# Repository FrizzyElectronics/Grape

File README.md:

# Grape

Grape es un Arduino&trade; compatible de fabricacion y diseño español. Destaca frente a otras placas por su rapidez de conexionado y por no necesitar el uso de protoboard para realizar los proyectos.

## Rasgos destacados

  - Conexion micro-USB
  - Corriente max de salida (5V) 2A
  - Pines de conexión rápida
  - Interruptor de encendido-apagado
  - 8 pines analogicos
  - Compatible con los shields de Arduino&trade; y con Arduino&trade; IDE

## Documentacion 

* **/Hardware** - Archivos de diseño en KiCad e Eagle, esquema en PDF
* **/Production** - Gerbers, BOM
* **/Design** - Logos, SVG 

Licencia
-------------------

Este producto es  **open source**! 

Por favor, revisa el archivo [LICENSE.md](https://github.com/FrizzyElectronics/Grape/blob/master/License.md) para más información. 

Si tiene alguna duda acerca del uso de esta licencia contatanos a traves de  info@frizzy.es

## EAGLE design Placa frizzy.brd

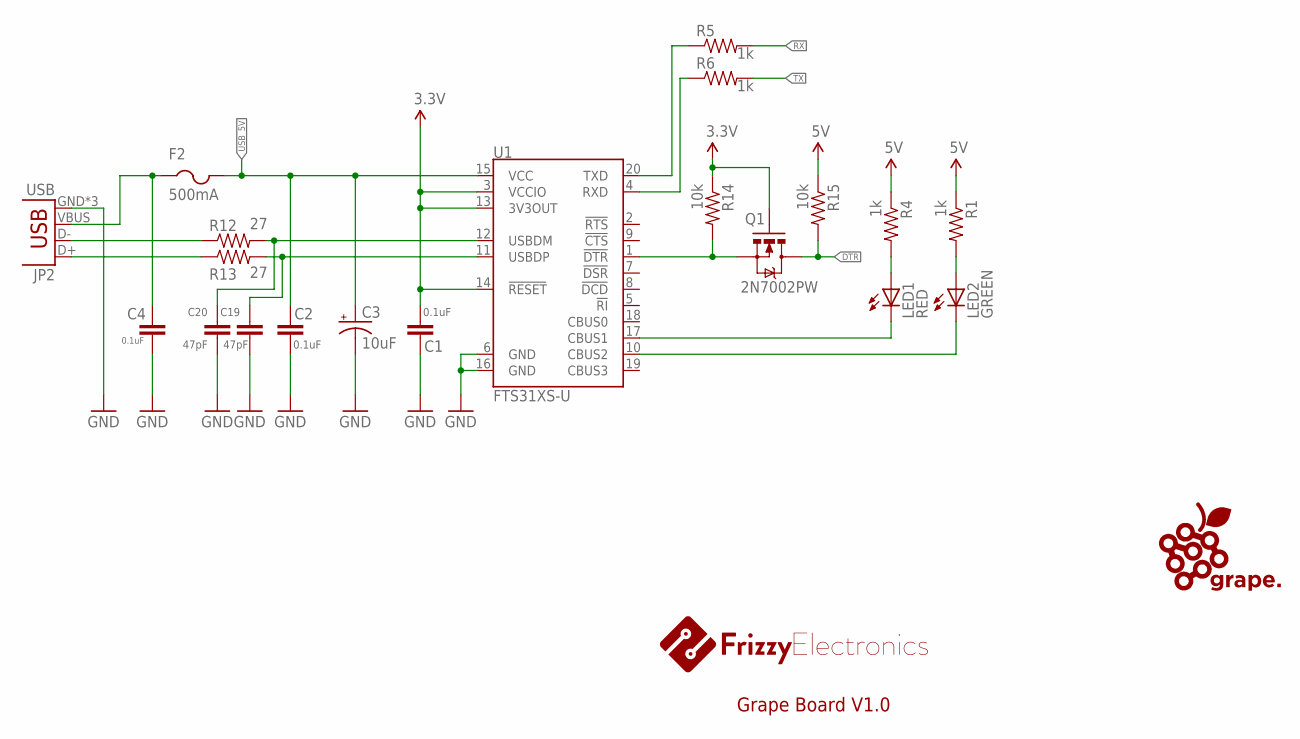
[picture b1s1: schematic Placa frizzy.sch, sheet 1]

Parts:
C1, C2, C4: 0.1uF; 0805
C3: 10uF; EIA3216
C19, C20: 47pF; 0805
F2: 500mA; 1812
JP2: USB; USB-MICROB
LED1: RED; CHIP-LED0805
LED2: GREEN; CHIP-LED0805
Q1: 2N7002PW; SOT323
R1, R4, R5, R6: 1k; 0805
R12, R13: 27; 0805
R14, R15: 10k; 0805
U1: FTS31XS-U; SSOP20_L

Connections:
3.3V: C1.2, Q1.1 (G), R14.1, U1.3 (VCCIO), U1.13 (3V3OUT), U1.14 (!RESET); also elsewhere on the board
DTR: Q1.3 (D), R15.2; also elsewhere on the board
GND: C1.1, C2.1, C3.C (-), C4.2, C19.1, C20.1, JP2.GND, JP2.MT1 (GND), JP2.MT2 (GND), U1.6 (GND), U1.16 (GND); also elsewhere on the board
unnamed: LED1.C, U1.17 (CBUS1)
unnamed: LED2.C, U1.10 (CBUS2)
unnamed: LED1.A, R4.2
unnamed: LED2.A, R1.2
unnamed: R5.1, U1.20 (TXD)
unnamed: R6.1, U1.4 (RXD)
unnamed: C20.2, R12.2, U1.12 (USBDM)
unnamed: Q1.2 (S), R14.2, U1.1 (!DTR)
unnamed: C19.2, R13.2, U1.11 (USBDP)
unnamed: JP2.D-, R12.1
unnamed: JP2.D+, R13.1
unnamed: C4.1, F2.1, JP2.VBUS
RX: R5.2; also elsewhere on the board
TX: R6.2; also elsewhere on the board
USB_5V: C2.2, C3.A (+), F2.2, U1.15 (VCC); also elsewhere on the board

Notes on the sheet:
Grape Board V1.0

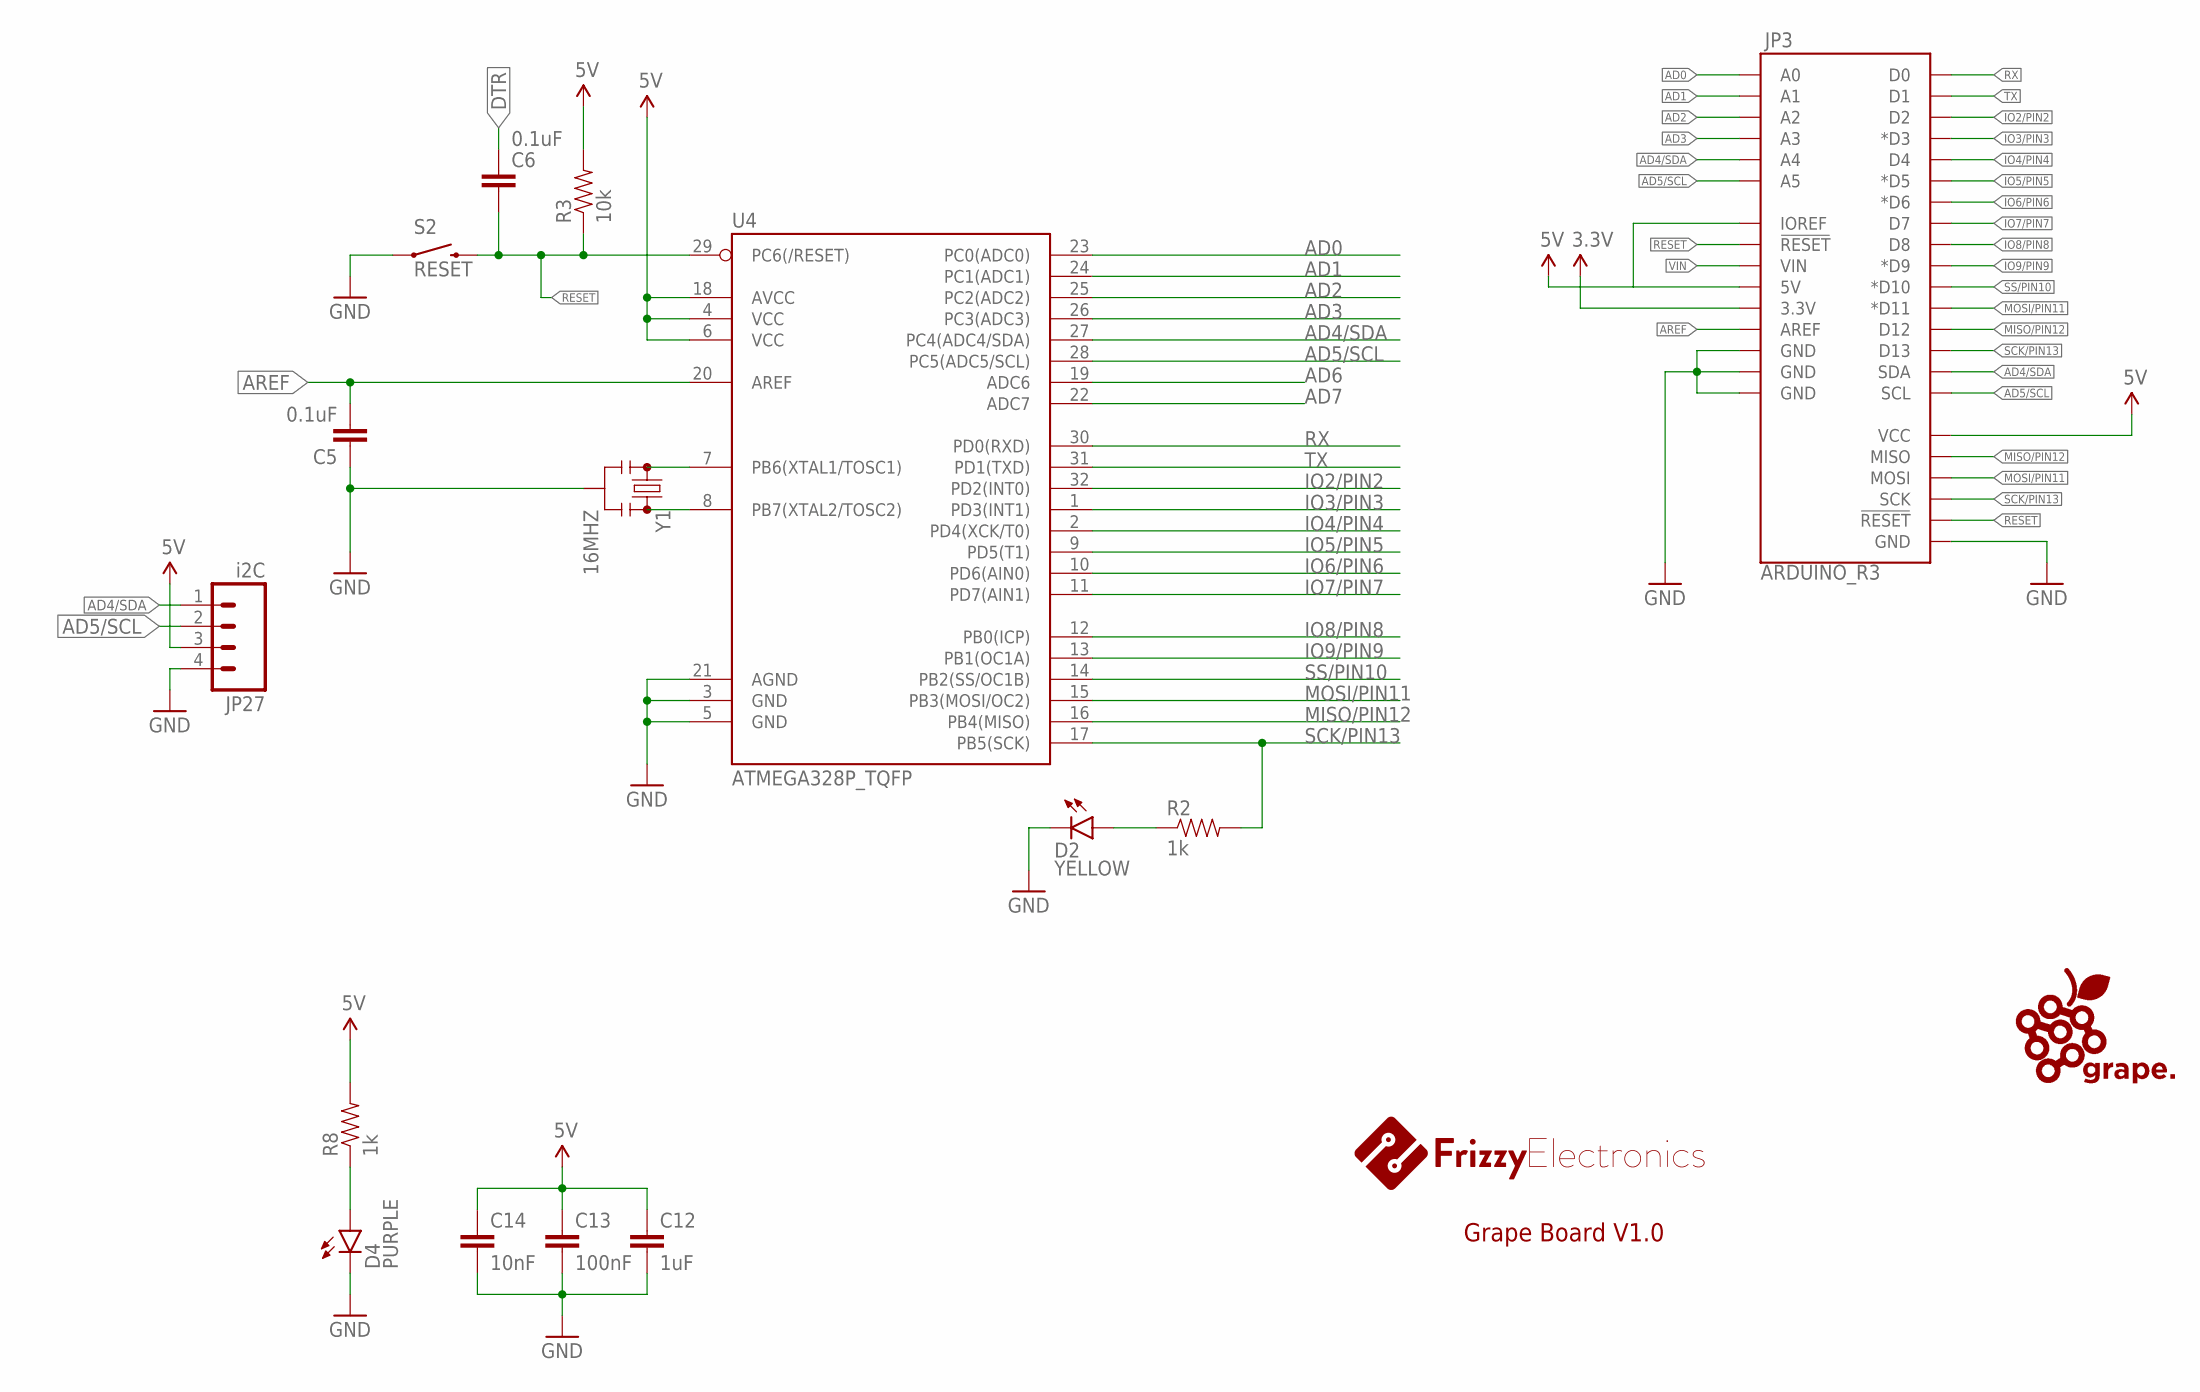
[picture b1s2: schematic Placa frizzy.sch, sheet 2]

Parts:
C5, C6: 0.1uF; 0603-CAP
C12: 1uF; 0603-CAP
C13: 100nF; 0603-CAP
C14: 10nF; 0603-CAP
D2: YELLOW; LED-0603
D4: PURPLE; LED-0603
JP3: ARDUINO_R3
JP27: i2C; JST-4-PTH
R2, R8: 1k; 0805
R3: 10k; 0805
S2: RESET; TACTILE-PTH-SIDEEZ
U4: ATMEGA328P_TQFP; TQFP32-08
Y1: 16MHZ; RESONATOR-SMD

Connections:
3.3V: JP3.3.3V; also elsewhere on the board
AD0: JP3.A0, U4.23 (PC0(ADC0)); also elsewhere on the board
AD1: JP3.A1, U4.24 (PC1(ADC1)); also elsewhere on the board
AD2: JP3.A2, U4.25 (PC2(ADC2)); also elsewhere on the board
AD3: JP3.A3, U4.26 (PC3(ADC3)); also elsewhere on the board
AD4/SDA: JP3.A4, JP3.SDA, JP27.1, U4.27 (PC4(ADC4/SDA)); also elsewhere on the board
AD5/SCL: JP3.A5, JP3.SCL, JP27.2, U4.28 (PC5(ADC5/SCL)); also elsewhere on the board
AD6: U4.19 (ADC6); also elsewhere on the board
AD7: U4.22 (ADC7); also elsewhere on the board
AREF: C5.2, JP3.AREF, U4.20 (AREF)
DTR: C6.1; also elsewhere on the board
GND: C5.1, C12.2, C13.2, C14.2, D2.C, D4.C, JP3.GND@1 (GND), JP3.GND@2 (GND), JP3.GND@3 (GND), JP3.GND@4 (GND), JP27.4, S2.1, U4.3 (GND), U4.5 (GND), U4.21 (AGND), Y1.2; also elsewhere on the board
IO2/PIN2: JP3.D2, U4.32 (PD2(INT0)); also elsewhere on the board
IO3/PIN3: JP3.D3 (*D3), U4.1 (PD3(INT1)); also elsewhere on the board
IO4/PIN4: JP3.D4, U4.2 (PD4(XCK/T0)); also elsewhere on the board
IO5/PIN5: JP3.D5 (*D5), U4.9 (PD5(T1)); also elsewhere on the board
IO6/PIN6: JP3.D6 (*D6), U4.10 (PD6(AIN0)); also elsewhere on the board
IO7/PIN7: JP3.D7, U4.11 (PD7(AIN1)); also elsewhere on the board
IO8/PIN8: JP3.D8, U4.12 (PB0(ICP)); also elsewhere on the board
IO9/PIN9: JP3.D9 (*D9), U4.13 (PB1(OC1A)); also elsewhere on the board
MISO/PIN12: JP3.D12, JP3.MISO, U4.16 (PB4(MISO)); also elsewhere on the board
MOSI/PIN11: JP3.D11 (*D11), JP3.MOSI, U4.15 (PB3(MOSI/OC2)); also elsewhere on the board
unnamed: D2.A, R2.1
unnamed: D4.A, R8.1
unnamed: U4.7 (PB6(XTAL1/TOSC1)), Y1.1
unnamed: U4.8 (PB7(XTAL2/TOSC2)), Y1.3
RESET: C6.2, JP3.RESET@1 (!RESET!), JP3.RESET@2 (!RESET!), R3.1, S2.2, U4.29 (PC6(/RESET))
RX: JP3.D0, U4.30 (PD0(RXD)); also elsewhere on the board
SCK/PIN13: JP3.D13, JP3.SCK, R2.2, U4.17 (PB5(SCK)); also elsewhere on the board
SS/PIN10: JP3.D10 (*D10), U4.14 (PB2(SS/OC1B)); also elsewhere on the board
TX: JP3.D1, U4.31 (PD1(TXD)); also elsewhere on the board
VIN: JP3.VIN; also elsewhere on the board

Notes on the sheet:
Grape Board V1.0

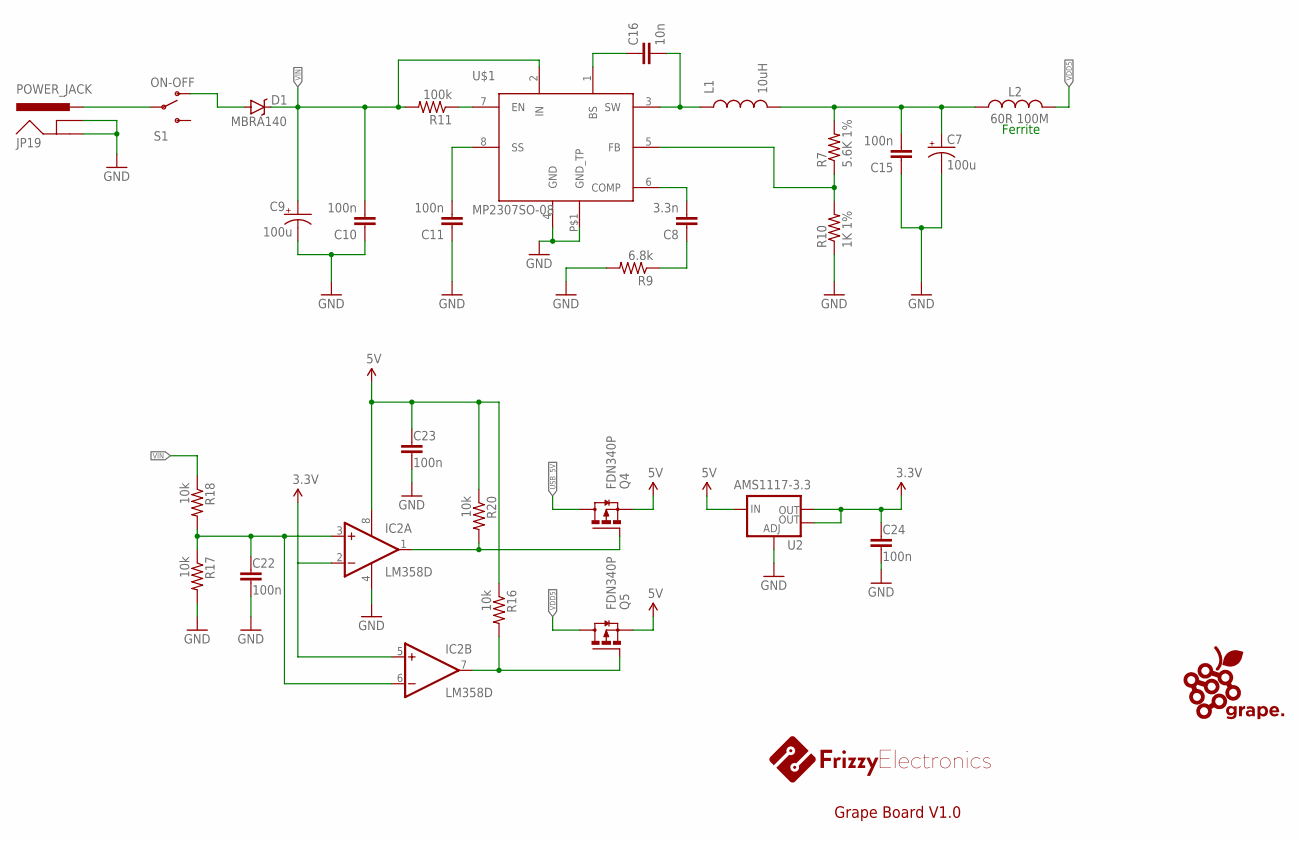
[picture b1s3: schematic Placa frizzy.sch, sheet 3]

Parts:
C7, C9: 100u; PANASONIC_D
C8: 3.3n; 0805
C10, C11, C15, C22, C23, C24: 100n; 0805
C16: 10n; 0805
D1: MBRA140; SMA-DIODE
IC2: LM358D; SO08
JP19: POWER_JACK; POWER_JACK_PTH
L1: 10uH; NPI75C
L2: 60R 100M; 0805
Q4, Q5: FDN340P; SUPER-SOT3
R7: 5.6K 1%; 0805
R9: 6.8k; 0805
R10: 1K 1%; 0805
R11: 100k; 0805
R16, R17, R18, R20: 10k; 0805
S1: ON-OFF; SWITCH-SPST-SMD-A
U2: AMS1117-3.3; SOT223
U$1: MP2307SO-08; SO-08

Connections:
3.3V: C24.1, IC2.2 (-IN), IC2.5 (+IN), U2.2 (OUT), U2.4 (OUT); also elsewhere on the board
GND: C7.-, C9.-, C10.1, C11.1, C15.1, C22.2, C23.2, C24.2, IC2.4 (V-), JP19.GND, JP19.GNDBREAK, R9.2, R10.1, R17.2, U2.1 (ADJ), U$1.4 (GND), U$1.P$1 (GND_TP); also elsewhere on the board
unnamed: C8.1, R9.1
unnamed: C8.2, U$1.6 (COMP)
unnamed: R7.1, R10.2, U$1.5 (FB)
unnamed: C16.1, U$1.1 (BS)
unnamed: C16.2, L1.1, U$1.3 (SW)
unnamed: C7.+, C15.2, L1.2, L2.1, R7.2
unnamed: C11.2, U$1.8 (SS)
unnamed: R11.1, U$1.7 (EN)
unnamed: JP19.PWR, S1.2
unnamed: D1.A, S1.1 (O)
unnamed: C22.1, IC2.3 (+IN), IC2.6 (-IN), R17.1, R18.2
unnamed: IC2.7 (OUT), Q5.1 (G), R16.2
unnamed: IC2.1 (OUT), Q4.1 (G), R20.2
USB_5V: Q4.3 (D); also elsewhere on the board
VDD5: L2.2, Q5.3 (D)
VIN: C9.+, C10.2, D1.C, R11.2, R18.1, U$1.2 (IN); also elsewhere on the board

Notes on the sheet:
Ferrite
Grape Board V1.0

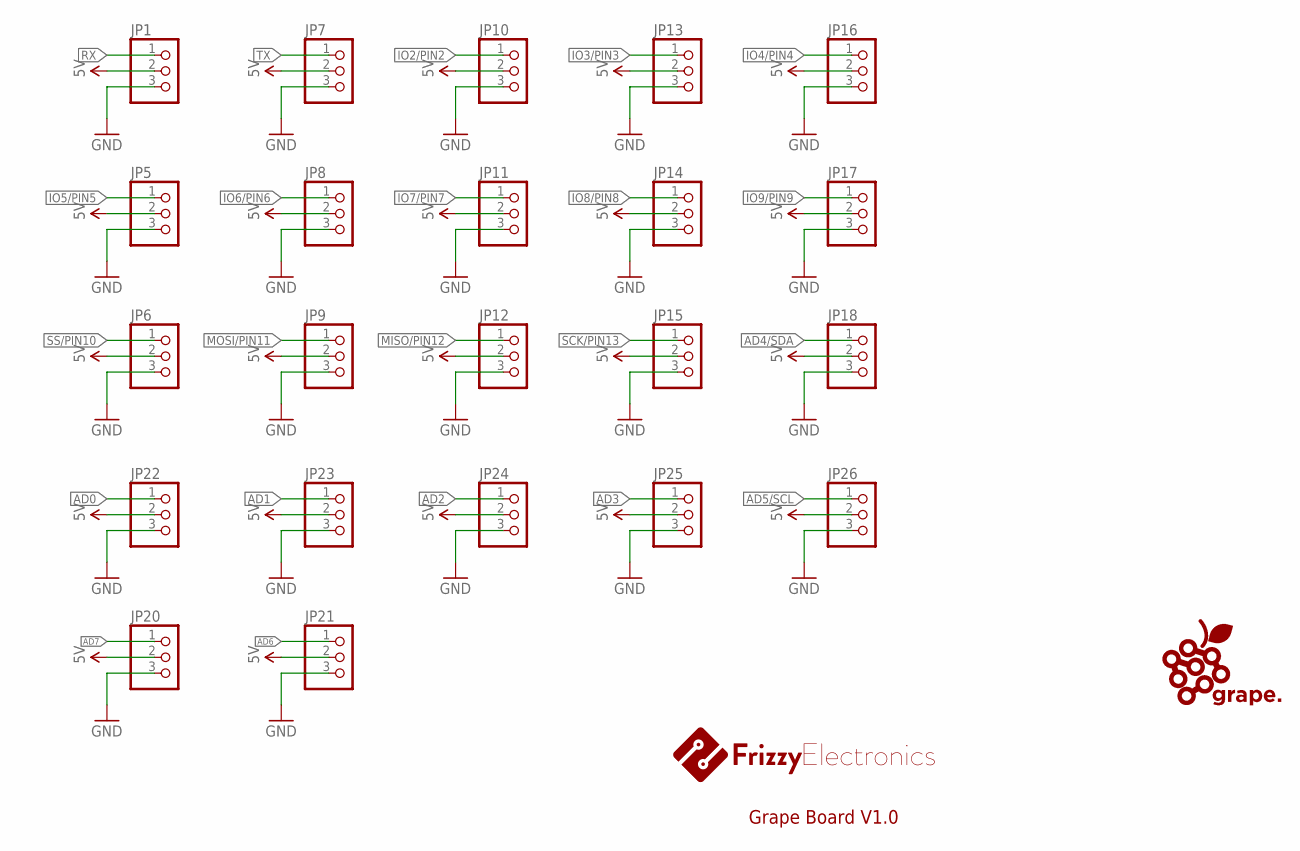
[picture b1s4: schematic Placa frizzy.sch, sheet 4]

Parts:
JP1, JP5, JP6, JP7, JP8, JP9, JP10, JP11, JP12, JP13, JP14, JP15, JP16, JP17, JP18, JP20, JP21, JP22, JP23, JP24, JP25, JP26: PINHD-1X3; 1X03

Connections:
AD0: JP22.1; also elsewhere on the board
AD1: JP23.1; also elsewhere on the board
AD2: JP24.1; also elsewhere on the board
AD3: JP25.1; also elsewhere on the board
AD4/SDA: JP18.1; also elsewhere on the board
AD5/SCL: JP26.1; also elsewhere on the board
AD6: JP21.1; also elsewhere on the board
AD7: JP20.1; also elsewhere on the board
GND: JP1.3, JP5.3, JP6.3, JP7.3, JP8.3, JP9.3, JP10.3, JP11.3, JP12.3, JP13.3, JP14.3, JP15.3, JP16.3, JP17.3, JP18.3, JP20.3, JP21.3, JP22.3, JP23.3, JP24.3, JP25.3, JP26.3; also elsewhere on the board
IO2/PIN2: JP10.1; also elsewhere on the board
IO3/PIN3: JP13.1; also elsewhere on the board
IO4/PIN4: JP16.1; also elsewhere on the board
IO5/PIN5: JP5.1; also elsewhere on the board
IO6/PIN6: JP8.1; also elsewhere on the board
IO7/PIN7: JP11.1; also elsewhere on the board
IO8/PIN8: JP14.1; also elsewhere on the board
IO9/PIN9: JP17.1; also elsewhere on the board
MISO/PIN12: JP12.1; also elsewhere on the board
MOSI/PIN11: JP9.1; also elsewhere on the board
RX: JP1.1; also elsewhere on the board
SCK/PIN13: JP15.1; also elsewhere on the board
SS/PIN10: JP6.1; also elsewhere on the board
TX: JP7.1; also elsewhere on the board

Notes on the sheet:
Grape Board V1.0

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
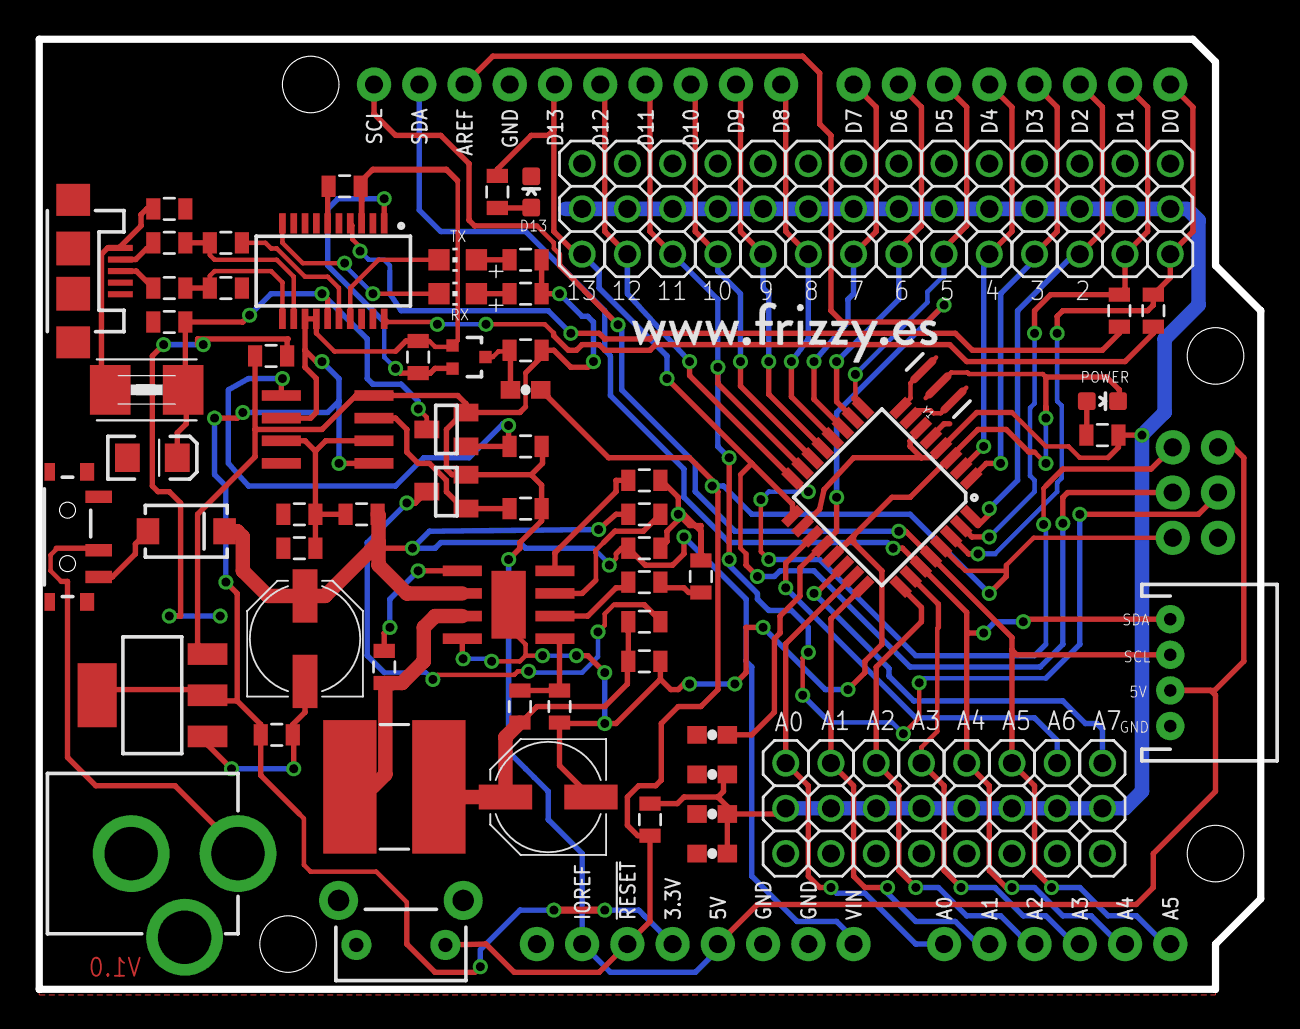
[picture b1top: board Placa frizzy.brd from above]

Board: 2 copper layers, 68.6 x 53.3 mm, 86 parts (1 on the bottom side), 61 nets.

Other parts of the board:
U$4: OSHW-LOGO-M

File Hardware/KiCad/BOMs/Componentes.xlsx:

Id | Identificador | Empaquetado | Cantidad | Identificación | Suministrador y ref
0 | C1,C2,C4,C10,C11,C15,C22,C23,C24 | C_0805 | 9 | 100nF
1 | C3 | CP_Tantalum_Case-A_EIA-3216-18_Reflow | 1 | 10nF
2 | C5,C6,C13 | C_0603 | 3 | 100nF
3 | C7,C9 | CP_Elec_6.3x5.3 | 2 | 100uF
4 | C8 | C_0805 | 1 | 3.3nF
5 | C12 | C_0603 | 1 | 1uF
6 | C14 | C_0603 | 1 | 10nF
7 | C16 | C_0805 | 1 | 10nF
8 | C19,C20 | C_0805 | 2 | 47pF
9 | D1 | D_SMA | 1 | MBRA140
10 | D2 | LED_0603 | 1 | YELLOW
11 | D4 | LED_0603 | 1 | PURPLE
12 | F2 | R_1812 | 1 | 500mA
13 | J19 | JACK_ALIM | 1 | POWER_JACKPTH
14 | L1 | L_Wurth_WE-PD2-Typ-L | 1 | 10uH
15 | L2 | L_0805 | 1 | 60R 100M Ferrite
16 | LED1 | LED_0805 | 1 | RED
17 | LED2 | LED_0805 | 1 | GREEN
18 | P1,P2,P3,P4,P5,P6,P7,P8,P9,P10,P11,P12,P13,P14,P15,P16,P17,P18,P19,P20,P21,P22 | Pin_Header_Straight_1x03_Pitch2.54mm | 22 | CONN_01X03
19 | P23 | JST_PH_S4B-PH-K_04x2.00mm_Angled | 1 | I2C
20 | Q1 | SOT-323_SC-70 | 1 | 2N7002PW
21 | Q4,Q5 | SOT-23 | 2 | FDN340P
22 | R1,R2,R4,R5,R6,R8 | R_0805 | 6 | 1k
23 | R3,R14,R15,R16,R17,R18,R20 | R_0805 | 7 | 10k
24 | R7 | R_0805 | 1 | 5K6 1%
25 | R9 | R_0805 | 1 | 6.8k
26 | R10 | R_0805 | 1 | 1k 1%
27 | R11 | R_0805 | 1 | 100k
28 | R12,R13 | R_0805 | 2 | 27R
29 | S2 | SW_Tactile_SPST_Angled_PTS645Vx39-2LFS | 1 | RESET
30 | SW1 | SW_SPDT_PCM12 | 1 | SW_SPDT
31 | U1 | SSOP-20 | 1 | FT231XS
32 | U2 | SOIC-8_3.9x4.9mm_Pitch1.27mm | 1 | LM358
33 | U3 | SOT-223 | 1 | AMS1117-3.3
34 | U4 | TQFP-32_7x7mm_Pitch0.8mm | 1 | ATMEGA328P_TQFP
35 | U8 | HTSOP-8-1EP_3.9x4.9mm_Pitch1.27mm_ThermalVias_LargeCopper | 1 | MP2307SO
36 | Y1 | RESONATOR-SMD-3.2X1.3 | 1 | 16MHz
37 | J1 | USB_Micro-B_Molex-105017-0001 | 1 | USB_MICROB

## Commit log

2016-08-02 Add files via upload
    Version 1.0
2016-11-19 Ultima version mandada a fabrica
2017-01-09 Vias Tapadas, USB cambiado, TX RX añadido
    se ha reparado tambien la alimentacion de 5V
2017-07-17 Ficheros de diseño añadidos
2017-07-17 Limpieza de archivos basura
2017-07-17 Iniciando la documentacion
2017-07-17 Readme añadido
2017-07-17 License added
2017-07-17 Svg añadido al readme
2018-01-14 Comenzando la migracion a kicad, esquema y hojas creadas
2018-01-14 Primera pagina terminada
2018-01-14 Microcontrolador añadido
2018-01-14 Alimentacion comenzada
2018-01-15 Alimentacion terminada
2018-01-15 Esquema terminado y ERC pasado
2018-01-15 cvpcb terminado
2018-01-15 Semiconductores colocados en placa y 3D añadido
2018-01-17 3D terminado
2018-01-17 Comenzado el enrutado
2018-01-25 copia de seguridad
2018-01-29 Enrutando la placa
2018-01-29 enrutado completo
2018-01-29 empezando con la serigrafia
2018-01-30 Avanzando con la serigrafia
2018-02-04 Serigrafia web añadida
2018-02-04 Usb cambiado
2018-02-04 Terminada
2018-04-22 Actualizado .gitignore y creado archivo .pro
2018-05-06 Cambiando el árbol de carpetas
2018-05-06 Carpeta limpada de .mod's
2018-05-06 3D enlazado y arbol de carpetas terminado
2018-05-13 Valores cambiados
2018-06-08 Añadida serigrafia en PWM pins
2018-06-08 Gerbers generados y mandado a fabrica para prueba
    Fabricado con JLCPCB a 1.2mm y sin merge
2018-07-14 Re-rellenado el plano de masa
2018-07-15 Gerbers exportados
2020-11-14 preparando archivos
2020-11-14 Prueba de guardado
2020-11-14 Conector y CH340C implementado
2020-11-14 Esquema terminado
    Falta comprobar

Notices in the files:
parts and their libraries:
SparkFun-Passives: Licensing: Creative Commons ShareAlike 4.0 International - https://creativecommons.org/licenses/by-sa/4.0
